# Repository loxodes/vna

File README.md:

# Open Hardware Vector Network Analyzer
I'm developing a proof of concept two port microwave vector network analyzer. The project is under developent.
[Ongoing documentation and logs are located on a hackaday.io project page.](https://hackaday.io/project/26213-vector-network-analyzer)

## Usage
This project is still under development, y'all probably don't want to try reproducing it yet.
Two port measurements to 14 GHz work, a redesign for operation out to 36 GHz is in progress.

## Hardware Design
See `breakouts` and `hardware` for various modules developed for the network analyzer.

## Software Design
See the `software` directory for scraps of software written for testing VNA modules. 

## License
Unless otherwise noted, all work is under a MIT license.

## Contact
Feel free to contact me at arcticmicrowave@gmail.com or loxodes on irc.freenode.net

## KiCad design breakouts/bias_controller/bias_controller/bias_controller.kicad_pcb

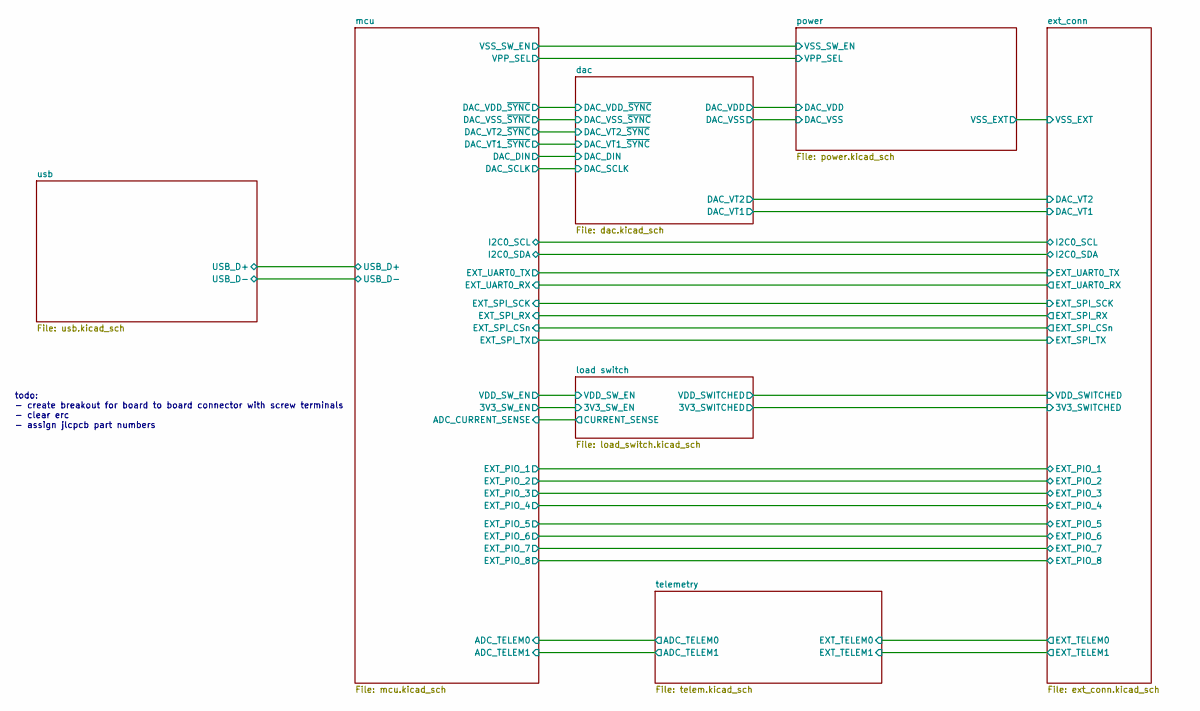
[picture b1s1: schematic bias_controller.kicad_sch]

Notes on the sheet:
todo: - create breakout for board to board connector with screw terminals - clear erc - assign jlcpcb part numbers

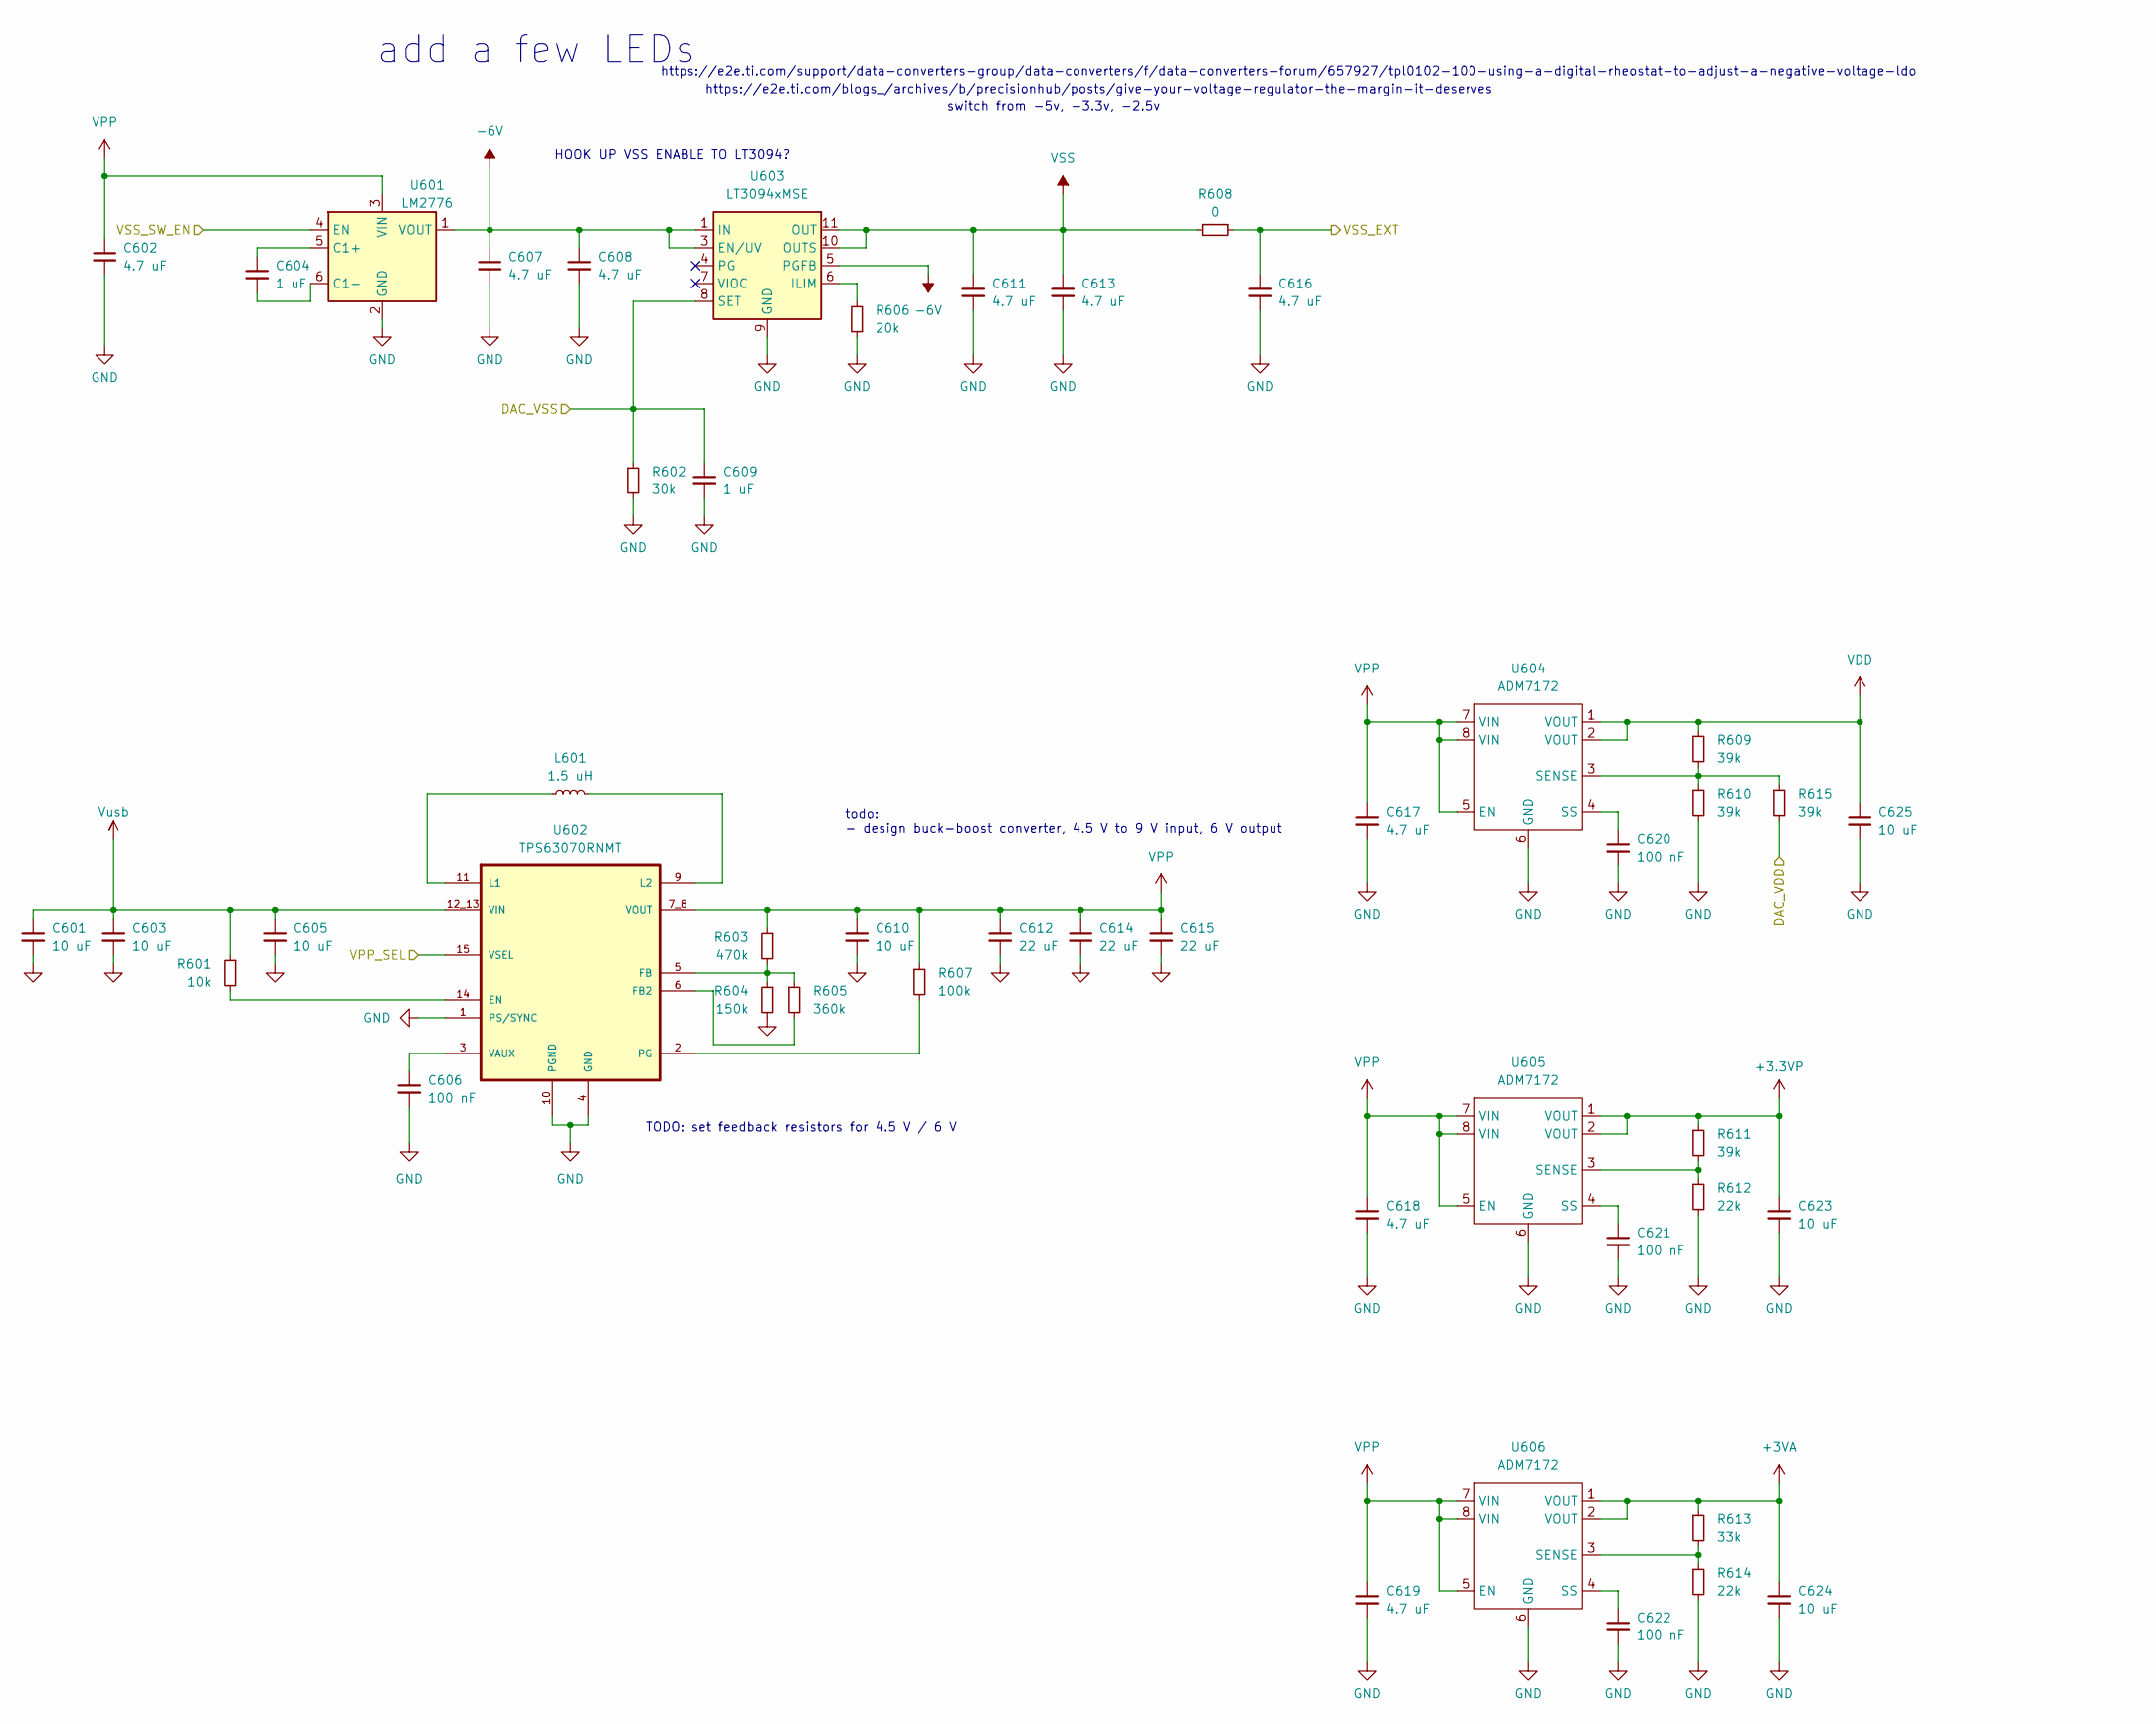
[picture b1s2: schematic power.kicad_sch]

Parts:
C601, C603, C605, C610, C623, C624, C625: 10 uF; C_0603_1608Metric
C602, C607, C608, C611, C613, C616, C617, C618, C619: 4.7 uF; C_0603_1608Metric
C604, C609: 1 uF; C_0402_1005Metric
C606, C620, C621, C622: 100 nF; C_0402_1005Metric
C612, C614, C615: 22 uF; C_0805_2012Metric
L601: 1.5 uH; L_Coilcraft_XxL4020
R601: 10k; R_0402_1005Metric
R602: 30k; R_0402_1005Metric
R603: 470k; R_0402_1005Metric
R604: 150k; R_0402_1005Metric
R605: 360k; R_0402_1005Metric
R606: 20k; R_0402_1005Metric
R607: 100k; R_0402_1005Metric
R608: 0; R_0402_1005Metric
R609, R610, R611, R615: 39k; R_0402_1005Metric
R612, R614: 22k; R_0402_1005Metric
R613: 33k; R_0402_1005Metric
U601: LM2776; SOT-23-6
U602: TPS63070RNMT; VREG_TPS63070RNMR
U603: LT3094xMSE; MSOP-12-1EP_3x4mm_P0.65mm_EP1.65x2.85mm
U604, U605, U606: ADM7172; LFCSP-8-1EP_3x3mm_P0.5mm_EP1.6x2.34mm

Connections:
+3.3VP: C623.1, R611.1, U605.1 (VOUT), U605.2 (VOUT); also elsewhere on the board
+3VA: C624.1, R613.1, U606.1 (VOUT), U606.2 (VOUT); also elsewhere on the board
-6V: C607.1, C608.1, U601.1 (VOUT), U603.1 (IN), U603.2 (IN), U603.3 (EN/UV), U603.5 (PGFB), U603.13 (IN); also elsewhere on the board
/dac/DAC_VDD: R615.2; also elsewhere on the board
/dac/DAC_VSS: C609.1, R602.1, U603.8 (SET); also elsewhere on the board
/ext_conn/VSS_EXT: C616.1, R608.1; also elsewhere on the board
/mcu/VPP_SEL: U602.15 (VSEL); also elsewhere on the board
/mcu/VSS_SW_EN: U601.4 (EN); also elsewhere on the board
GND: C601.2, C602.2, C603.2, C605.2, C606.2, C607.2, C608.2, C609.2, C610.2, C611.2, C612.2, C613.2, C614.2, C615.2, C616.2, C617.2, C618.2, C619.2, C620.2, C621.2, C622.2, C623.2, C624.2, C625.2, R602.2, R604.2, R606.1, R610.2, R612.2, R614.2, U601.2 (GND), U602.1 (PS/SYNC), U602.4 (GND), U602.10 (PGND), U603.9 (GND), U604.6 (GND), U604.9 (GND), U605.6 (GND), U605.9 (GND), U606.6 (GND), U606.9 (GND); also elsewhere on the board
unnamed: C604.1, U601.5 (C1+)
unnamed: C604.2, U601.6 (C1-)
unnamed: R601.2, U602.14 (EN)
unnamed: R605.2, U602.6 (FB2)
unnamed: R603.2, R604.1, R605.1, U602.5 (FB)
unnamed: L601.1, U602.11 (L1)
unnamed: L601.2, U602.9 (L2)
unnamed: R607.2, U602.2 (PG)
unnamed: C606.1, U602.3 (VAUX)
unnamed: R606.2, U603.6 (ILIM)
unnamed: R609.2, R610.1, R615.1, U604.3 (SENSE)
unnamed: C620.1, U604.4 (SS)
unnamed: R611.2, R612.1, U605.3 (SENSE)
unnamed: C621.1, U605.4 (SS)
unnamed: R613.2, R614.1, U606.3 (SENSE)
unnamed: C622.1, U606.4 (SS)
VDD: C625.1, R609.1, U604.1 (VOUT), U604.2 (VOUT); also elsewhere on the board
VPP: C602.1, C610.1, C612.1, C614.1, C615.1, C617.1, C618.1, C619.1, R603.1, R607.1, U601.3 (VIN), U602.7_8 (VOUT), U604.5 (EN), U604.7 (VIN), U604.8 (VIN), U605.5 (EN), U605.7 (VIN), U605.8 (VIN), U606.5 (EN), U606.7 (VIN), U606.8 (VIN); also elsewhere on the board
VSS: C611.1, C613.1, R608.2, U603.10 (OUTS), U603.11 (OUT), U603.12 (OUT)
Vusb: C601.1, C603.1, C605.1, R601.1, U602.12_13 (VIN); also elsewhere on the board

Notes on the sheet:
TODO: set feedback resistors for 4.5 V / 6 V
https://e2e.ti.com/support/data-converters-group/data-converters/f/data-converters-forum/657927/tpl0102-100-using-a-digital-rheostat-to-adjust-a-negative-voltage-ldo
switch from -5v, -3.3v, -2.5v
HOOK UP VSS ENABLE TO LT3094?
add a few LEDs
https://e2e.ti.com/blogs_/archives/b/precisionhub/posts/give-your-voltage-regulator-the-margin-it-deserves
todo: - design buck-boost converter, 4.5 V to 9 V input, 6 V output

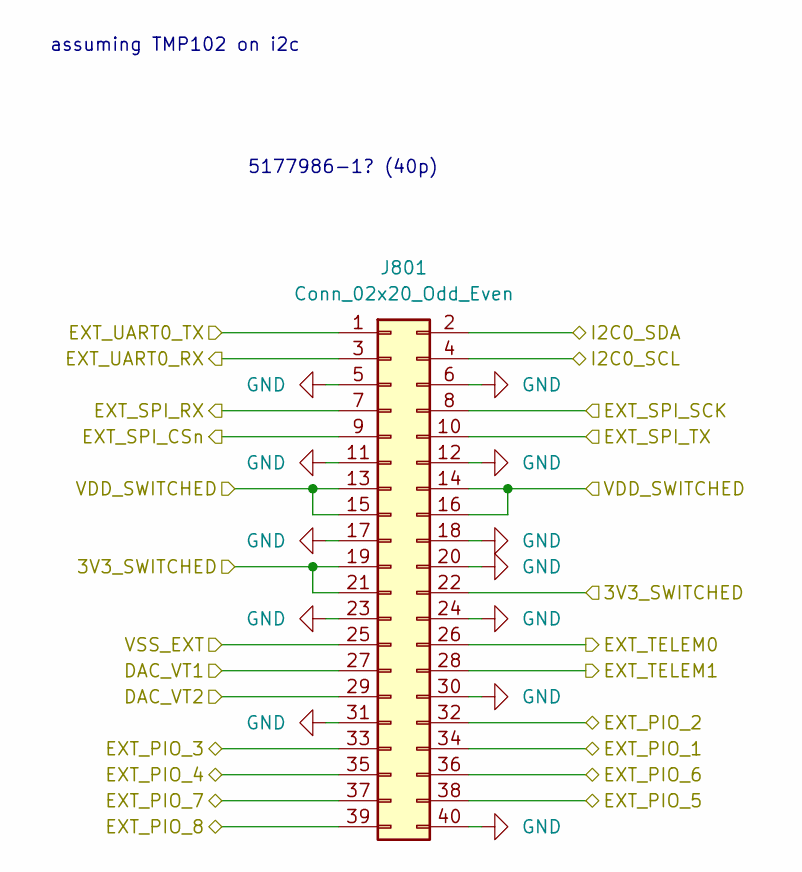
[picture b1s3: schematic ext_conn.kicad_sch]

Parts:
J801: Conn_02x20_Odd_Even; TE_5177986-1

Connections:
/dac/DAC_VT1: J801.27; also elsewhere on the board
/dac/DAC_VT2: J801.29; also elsewhere on the board
/ext_conn/3V3_SWITCHED: J801.19, J801.21, J801.22; also elsewhere on the board
/ext_conn/EXT_PIO_1: J801.34; also elsewhere on the board
/ext_conn/EXT_PIO_2: J801.32; also elsewhere on the board
/ext_conn/EXT_PIO_3: J801.33; also elsewhere on the board
/ext_conn/EXT_PIO_4: J801.35; also elsewhere on the board
/ext_conn/EXT_PIO_5: J801.38; also elsewhere on the board
/ext_conn/EXT_PIO_6: J801.36; also elsewhere on the board
/ext_conn/EXT_PIO_7: J801.37; also elsewhere on the board
/ext_conn/EXT_PIO_8: J801.39; also elsewhere on the board
/ext_conn/EXT_SPI_CSn: J801.9; also elsewhere on the board
/ext_conn/EXT_SPI_RX: J801.7; also elsewhere on the board
/ext_conn/EXT_SPI_SCK: J801.8; also elsewhere on the board
/ext_conn/EXT_SPI_TX: J801.10; also elsewhere on the board
/ext_conn/EXT_TELEM0: J801.26; also elsewhere on the board
/ext_conn/EXT_TELEM1: J801.28; also elsewhere on the board
/ext_conn/EXT_UART0_RX: J801.3; also elsewhere on the board
/ext_conn/EXT_UART0_TX: J801.1; also elsewhere on the board
/ext_conn/VDD_SWITCHED: J801.13, J801.14, J801.15, J801.16; also elsewhere on the board
/ext_conn/VSS_EXT: J801.25; also elsewhere on the board
/mcu/SCL: J801.4; also elsewhere on the board
/mcu/SDA: J801.2; also elsewhere on the board
GND: J801.5, J801.6, J801.11, J801.12, J801.17, J801.18, J801.20, J801.23, J801.24, J801.30, J801.31, J801.40; also elsewhere on the board

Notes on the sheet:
assuming TMP102 on i2c
5177986-1? (40p)

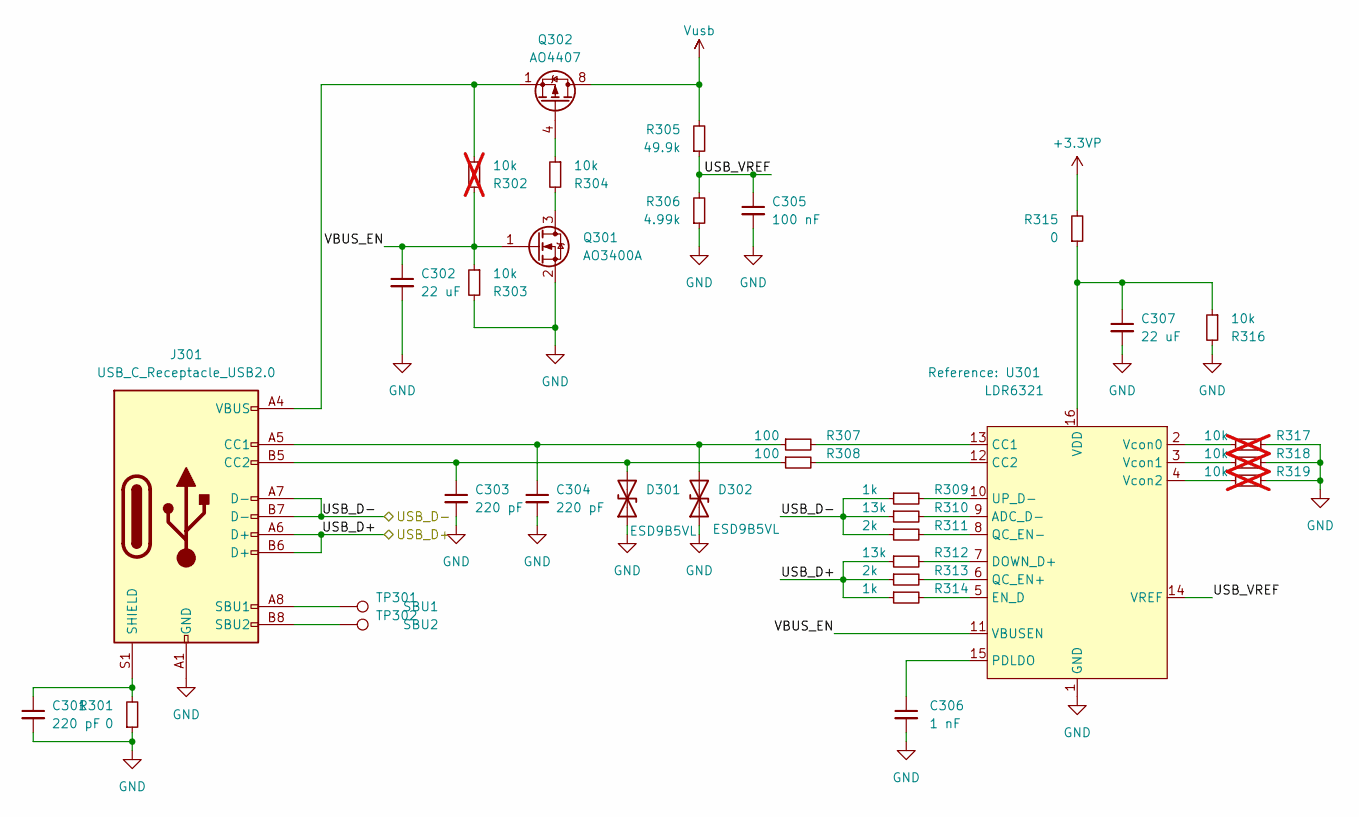
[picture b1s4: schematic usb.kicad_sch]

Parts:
C301, C303, C304: 220 pF; C_0402_1005Metric
C302: 22 uF; C_0805_2012Metric
C305: 100 nF; C_0402_1005Metric
C306: 1 nF; C_0402_1005Metric
C307: 22 uF; C_0603_1608Metric
D301, D302: ESD9B5VL; DFN1006-2
J301: USB_C_Receptacle_USB2.0; USB_C_Receptacle_G-Switch_GT-USB-7010ASV
Q301: AO3400A; SOT-23
Q302: AO4407; SOIC-8_3.9x4.9mm_P1.27mm
R301, R315: 0; R_0402_1005Metric
R302, R317, R318, R319: 10k; R_0402_1005Metric; not fitted
R303, R304, R316: 10k; R_0402_1005Metric
R305: 49.9k; R_0402_1005Metric
R306: 4.99k; R_0402_1005Metric
R307, R308: 100; R_0402_1005Metric
R309, R314: 1k; R_0402_1005Metric
R310, R312: 13k; R_0402_1005Metric
R311, R313: 2k; R_0402_1005Metric
TP301: SBU1; TestPoint_Pad_D1.0mm
TP302: SBU2; TestPoint_Pad_D1.0mm
U301: LDR6321; SSOP-16_4.4x5.2mm_P0.65mm

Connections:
+3.3VP: R315.2; also elsewhere on the board
/usb/USB_D+: J301.A6 (D+), J301.B6 (D+), R312.1, R313.1, R314.1; also elsewhere on the board
/usb/USB_D-: J301.A7 (D-), J301.B7 (D-), R309.1, R310.1, R311.1; also elsewhere on the board
/usb/USB_VREF: C305.1, R305.1, R306.2, U301.14 (VREF)
/usb/VBUS_EN: C302.1, Q301.1 (G), R302.2, R303.1, U301.11 (VBUSEN)
GND: C301.2, C302.2, C303.2, C304.2, C305.2, C306.2, C307.2, D301.1 (A1), D302.1 (A1), J301.A1 (GND), J301.A12 (GND), J301.B1 (GND), J301.B12 (GND), Q301.2 (S), R301.1, R303.2, R306.1, R316.2, R317.2, R318.2, R319.2, U301.1 (GND); also elsewhere on the board
unnamed: C303.1, D301.2 (A2), J301.B5 (CC2), R308.1
unnamed: C304.1, D302.2 (A2), J301.A5 (CC1), R307.1
unnamed: J301.A8 (SBU1), TP301.1
unnamed: J301.B8 (SBU2), TP302.1
unnamed: C301.1, J301.S1 (SHIELD), R301.2
unnamed: J301.A4 (VBUS), J301.A9 (VBUS), J301.B4 (VBUS), J301.B9 (VBUS), Q302.1 (S), Q302.2 (S), Q302.3 (S), R302.1
unnamed: Q301.3 (D), R304.2
unnamed: Q302.4 (G), R304.1
unnamed: R310.2, U301.9 (ADC_D-)
unnamed: R307.2, U301.13 (CC1)
unnamed: R308.2, U301.12 (CC2)
unnamed: R312.2, U301.7 (DOWN_D+)
unnamed: R314.2, U301.5 (EN_D)
unnamed: C306.1, U301.15 (PDLDO)
unnamed: R313.2, U301.6 (QC_EN+)
unnamed: R311.2, U301.8 (QC_EN-)
unnamed: R309.2, U301.10 (UP_D-)
unnamed: C307.1, R315.1, R316.1, U301.16 (VDD)
unnamed: R317.1, U301.2 (Vcon0)
unnamed: R318.1, U301.3 (Vcon1)
unnamed: R319.1, U301.4 (Vcon2)
Vusb: Q302.5 (D), Q302.6 (D), Q302.7 (D), Q302.8 (D), R305.2; also elsewhere on the board

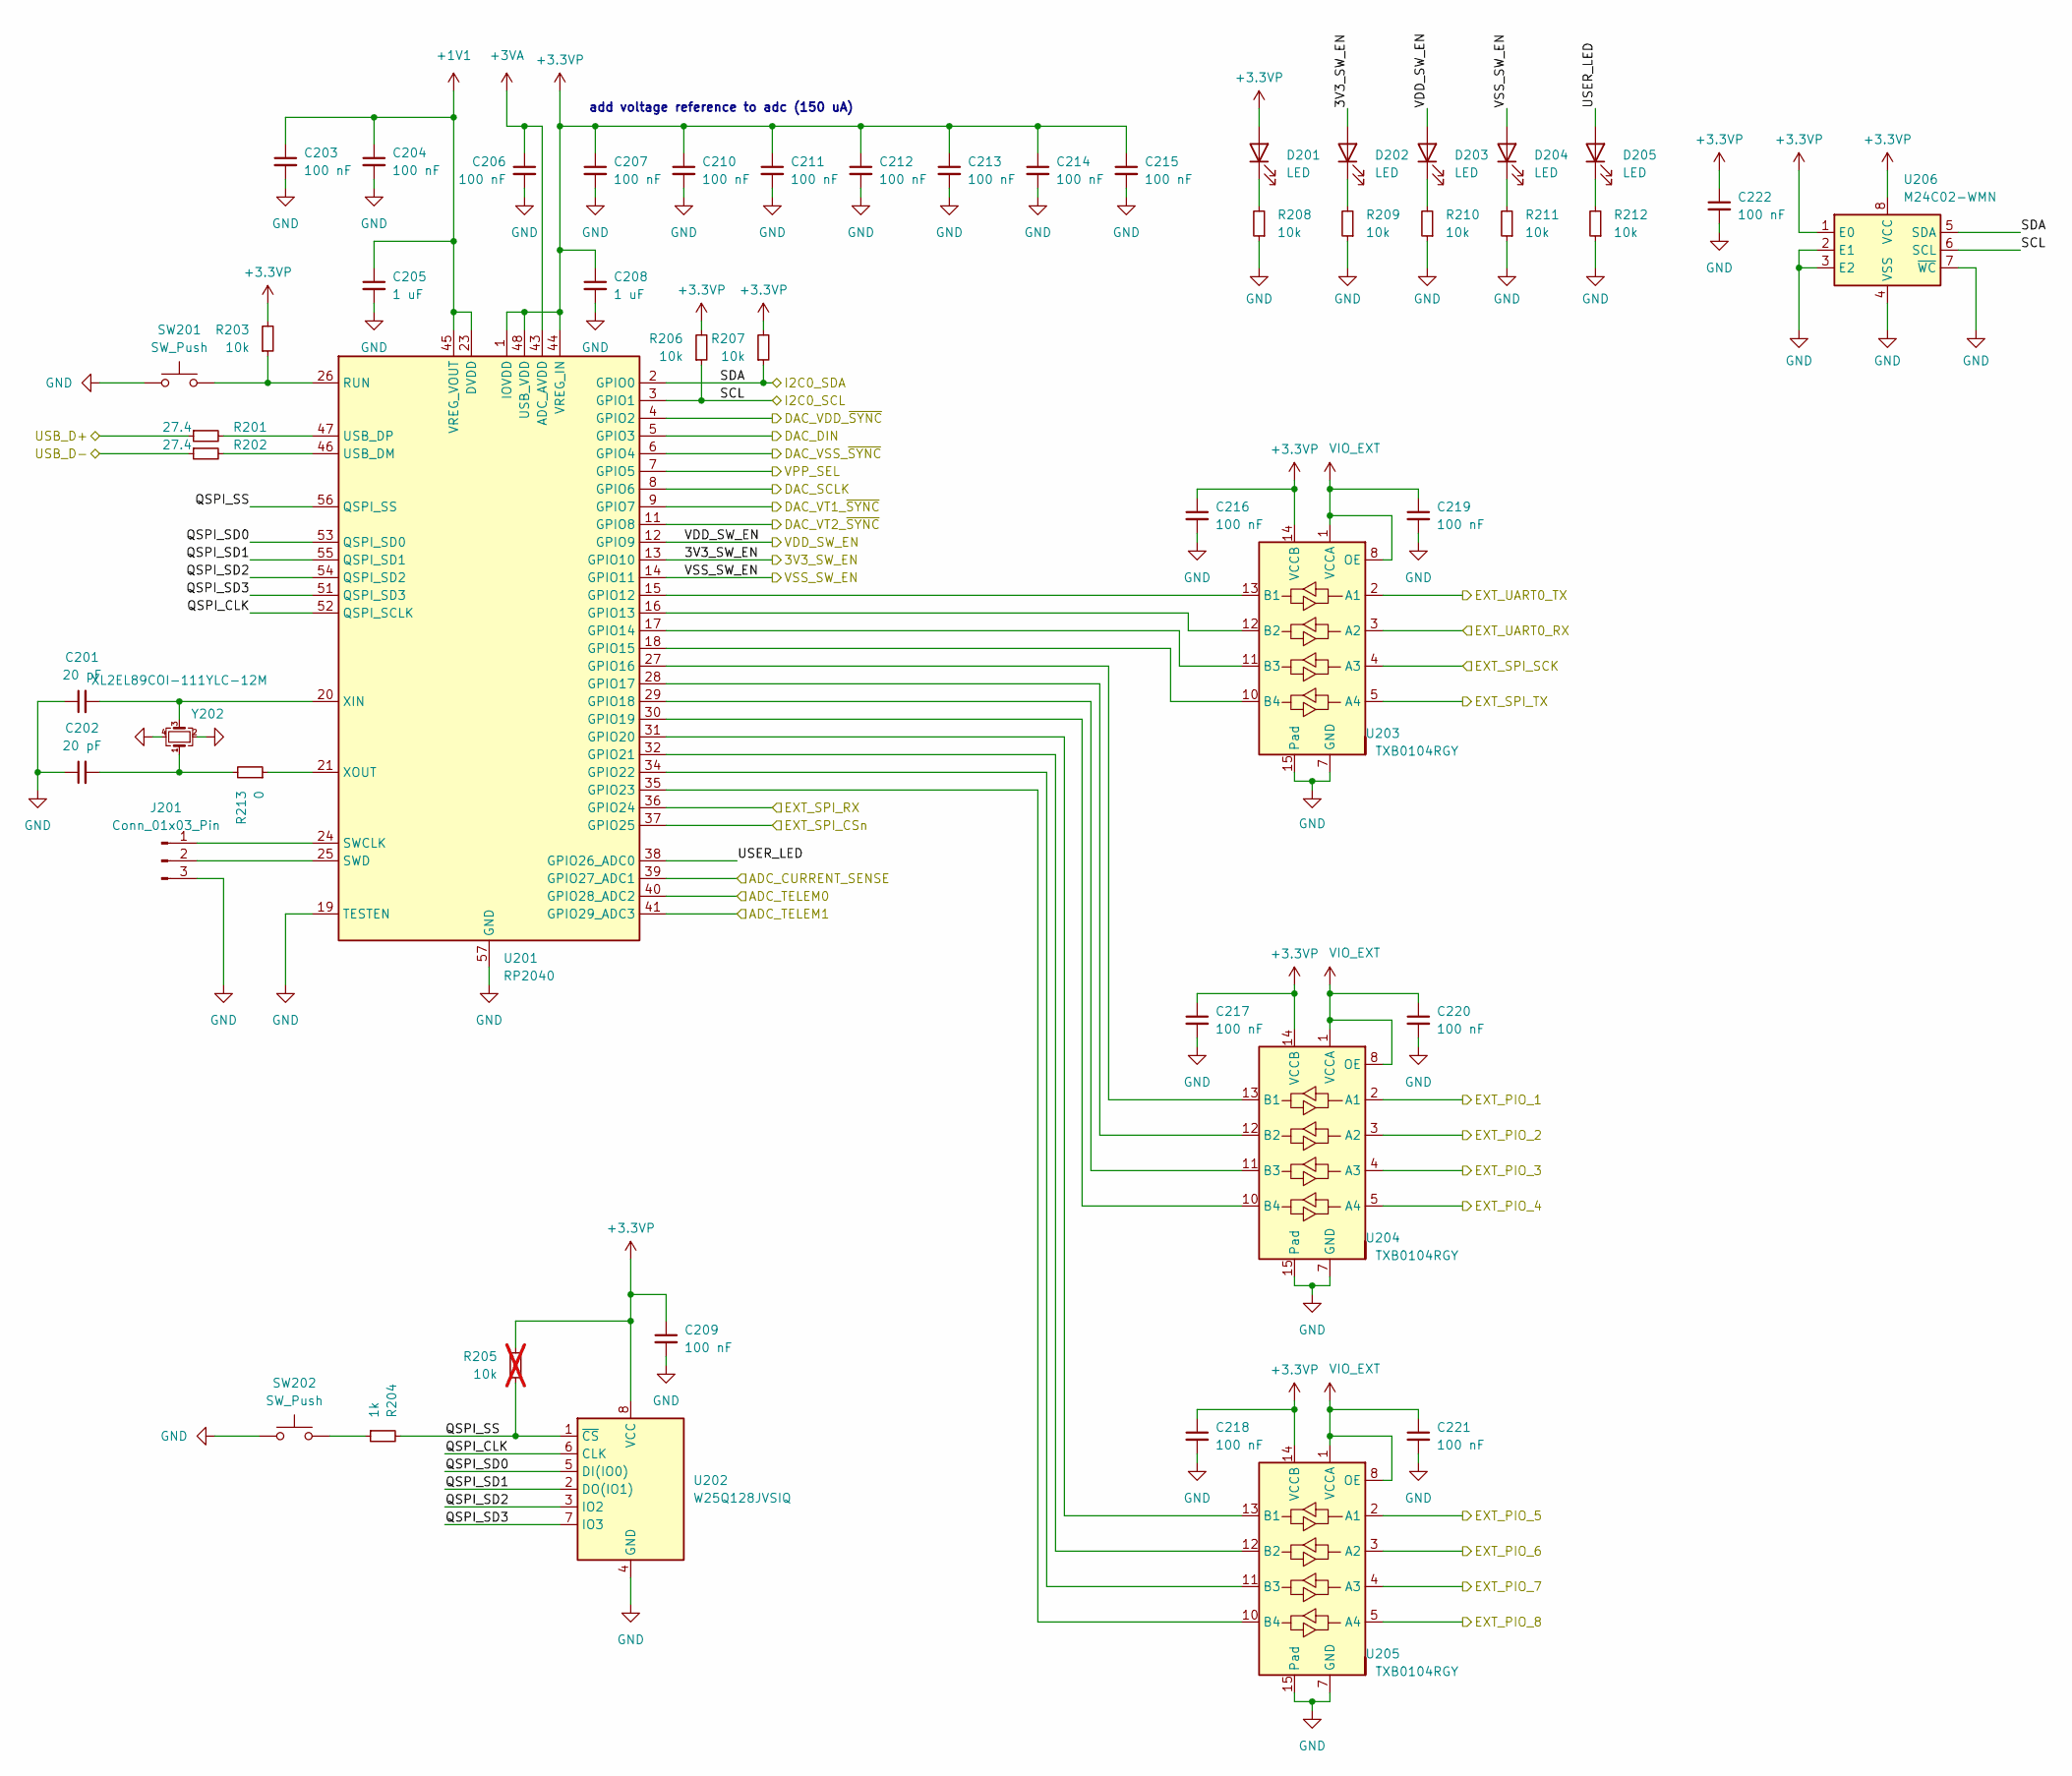
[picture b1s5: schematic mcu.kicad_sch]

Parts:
C201, C202: 20 pF; C_0402_1005Metric
C203, C204, C206, C207, C209, C210, C211, C212, C213, C214, C215, C216, C217, C218, C219, C220, C221, C222: 100 nF; C_0402_1005Metric
C205, C208: 1 uF; C_0402_1005Metric
D201, D202, D203, D204, D205: LED; LED_0603_1608Metric
J201: Conn_01x03_Pin; PinHeader_1x03_P2.54mm_Vertical
R201, R202: 27.4; R_0402_1005Metric
R203, R206, R207, R208, R209, R210, R211, R212: 10k; R_0402_1005Metric
R204: 1k; R_0402_1005Metric
R205: 10k; R_0402_1005Metric; not fitted
R213: 0; R_0402_1005Metric
SW201, SW202: SW_Push; SW_Push_1P1T_XKB_TS-1187A
U201: RP2040; QFN-56-1EP_7x7mm_P0.4mm_EP3.2x3.2mm
U202: W25Q128JVSIQ; SOIC-8_5.23x5.23mm_P1.27mm
U203, U204, U205: TXB0104RGY; Texas_S-PVQFN-N14
U206: M24C02-WMN; SOIC-8_3.9x4.9mm_P1.27mm
Y202: XL2EL89COI-111YLC-12M; Crystal_SMD_3225-4Pin_3.2x2.5mm

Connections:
+1V1: C203.1, C204.1, C205.1, U201.23 (DVDD), U201.45 (VREG_VOUT), U201.50 (DVDD)
+3.3VP: C207.1, C208.1, C209.1, C210.1, C211.1, C212.1, C213.1, C214.1, C215.1, C216.1, C217.1, C218.1, C222.1, D201.2 (A), R203.2, R205.2, R206.2, R207.2, U201.1 (IOVDD), U201.10 (IOVDD), U201.22 (IOVDD), U201.33 (IOVDD), U201.42 (IOVDD), U201.44 (VREG_IN), U201.48 (USB_VDD), U201.49 (IOVDD), U202.8 (VCC), U203.14 (VCCB), U204.14 (VCCB), U205.14 (VCCB), U206.1 (E0), U206.8 (VCC); also elsewhere on the board
+3VA: C206.1, U201.43 (ADC_AVDD); also elsewhere on the board
/dac/DAC_DIN: U201.5 (GPIO3); also elsewhere on the board
/dac/DAC_SCLK: U201.8 (GPIO6); also elsewhere on the board
/dac/DAC_VDD_~SYNC: U201.4 (GPIO2); also elsewhere on the board
/dac/DAC_VSS_~SYNC: U201.6 (GPIO4); also elsewhere on the board
/dac/DAC_VT1_~SYNC: U201.9 (GPIO7); also elsewhere on the board
/dac/DAC_VT2_~SYNC: U201.11 (GPIO8); also elsewhere on the board
/ext_conn/EXT_PIO_1: U204.2 (A1); also elsewhere on the board
/ext_conn/EXT_PIO_2: U204.3 (A2); also elsewhere on the board
/ext_conn/EXT_PIO_3: U204.4 (A3); also elsewhere on the board
/ext_conn/EXT_PIO_4: U204.5 (A4); also elsewhere on the board
/ext_conn/EXT_PIO_5: U205.2 (A1); also elsewhere on the board
/ext_conn/EXT_PIO_6: U205.3 (A2); also elsewhere on the board
/ext_conn/EXT_PIO_7: U205.4 (A3); also elsewhere on the board
/ext_conn/EXT_PIO_8: U205.5 (A4); also elsewhere on the board
/ext_conn/EXT_SPI_CSn: U201.37 (GPIO25); also elsewhere on the board
/ext_conn/EXT_SPI_RX: U201.36 (GPIO24); also elsewhere on the board
/ext_conn/EXT_SPI_SCK: U203.4 (A3); also elsewhere on the board
/ext_conn/EXT_SPI_TX: U203.5 (A4); also elsewhere on the board
/ext_conn/EXT_UART0_RX: U203.3 (A2); also elsewhere on the board
/ext_conn/EXT_UART0_TX: U203.2 (A1); also elsewhere on the board
/load switch/CURRENT_SENSE: U201.39 (GPIO27_ADC1); also elsewhere on the board
/mcu/3V3_SW_EN: D202.2 (A), U201.13 (GPIO10); also elsewhere on the board
/mcu/ADC_TELEM0: U201.40 (GPIO28_ADC2); also elsewhere on the board
/mcu/ADC_TELEM1: U201.41 (GPIO29_ADC3); also elsewhere on the board
/mcu/QSPI_CLK: U201.52 (QSPI_SCLK), U202.6 (CLK)
/mcu/QSPI_SD0: U201.53 (QSPI_SD0), U202.5 (DI(IO0))
/mcu/QSPI_SD1: U201.55 (QSPI_SD1), U202.2 (DO(IO1))
/mcu/QSPI_SD2: U201.54 (QSPI_SD2), U202.3 (IO2)
/mcu/QSPI_SD3: U201.51 (QSPI_SD3), U202.7 (IO3)
/mcu/QSPI_SS: R204.2, R205.1, U201.56 (QSPI_SS), U202.1 (~CS)
/mcu/SCL: R206.1, U201.3 (GPIO1), U206.6 (SCL); also elsewhere on the board
/mcu/SDA: R207.1, U201.2 (GPIO0), U206.5 (SDA); also elsewhere on the board
/mcu/USER_LED: D205.2 (A), U201.38 (GPIO26_ADC0)
/mcu/VDD_SW_EN: D203.2 (A), U201.12 (GPIO9); also elsewhere on the board
/mcu/VPP_SEL: U201.7 (GPIO5); also elsewhere on the board
/mcu/VSS_SW_EN: D204.2 (A), U201.14 (GPIO11); also elsewhere on the board
/usb/USB_D+: R201.1; also elsewhere on the board
/usb/USB_D-: R202.1; also elsewhere on the board
GND: C201.1, C202.1, C203.2, C204.2, C205.2, C206.2, C207.2, C208.2, C209.2, C210.2, C211.2, C212.2, C213.2, C214.2, C215.2, C216.2, C217.2, C218.2, C219.2, C220.2, C221.2, C222.2, J201.3, R208.1, R209.1, R210.1, R211.1, R212.1, SW201.1, SW202.1, U201.19 (TESTEN), U201.57 (GND), U202.4 (GND), U203.7 (GND), U203.15 (Pad), U204.7 (GND), U204.15 (Pad), U205.7 (GND), U205.15 (Pad), U206.2 (E1), U206.3 (E2), U206.4 (VSS), U206.7 (~WC), Y202.2, Y202.4; also elsewhere on the board
unnamed: C202.2, R213.2, Y202.1
unnamed: D201.1 (K), R208.2
unnamed: D202.1 (K), R209.2
unnamed: D203.1 (K), R210.2
unnamed: D204.1 (K), R211.2
unnamed: D205.1 (K), R212.2
unnamed: J201.1, U201.24 (SWCLK)
unnamed: J201.2, U201.25 (SWD)
unnamed: R204.1, SW202.2
unnamed: U201.15 (GPIO12), U203.13 (B1)
unnamed: U201.16 (GPIO13), U203.12 (B2)
unnamed: U201.17 (GPIO14), U203.11 (B3)
unnamed: U201.18 (GPIO15), U203.10 (B4)
unnamed: U201.27 (GPIO16), U204.13 (B1)
unnamed: U201.28 (GPIO17), U204.12 (B2)
unnamed: U201.29 (GPIO18), U204.11 (B3)
unnamed: U201.30 (GPIO19), U204.10 (B4)
unnamed: U201.31 (GPIO20), U205.13 (B1)
unnamed: U201.32 (GPIO21), U205.12 (B2)
unnamed: U201.34 (GPIO22), U205.11 (B3)
unnamed: U201.35 (GPIO23), U205.10 (B4)
unnamed: R203.1, SW201.2, U201.26 (RUN)
unnamed: R202.2, U201.46 (USB_DM)
unnamed: R201.2, U201.47 (USB_DP)
unnamed: C201.2, U201.20 (XIN), Y202.3
unnamed: R213.1, U201.21 (XOUT)
VIO_EXT: C219.1, C220.1, C221.1, U203.1 (VCCA), U203.8 (OE), U204.1 (VCCA), U204.8 (OE), U205.1 (VCCA), U205.8 (OE)

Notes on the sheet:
add voltage reference to adc (150 uA)
